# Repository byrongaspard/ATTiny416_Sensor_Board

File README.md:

# ATTiny416 Dev Board

This project is my first attempt at embedded hardware/software design where I layout/route a custom PCB. In my professional career, I have done schematic capture, integrated Arduino and Raspberry Pi like development boards into custom solutions, and developed embedded software, but this will be my first time laying out a custom circuit card.

There were no real requirements for this design as the primary objective was to learn how to layout a PCB using KiCad. However, to make the design process a little more interesting, I decided I wanted the board to have the following features:

- USB to UART communication to/from the microcontroller
- 3.3V microcontroller (instead of 5V)
- Includes SPI flash for recording data
- Accepts/regulates power from multiple inputs:
  - 5 V from USB
  - 30V from an external power source

The following image is the of the final board. The sections that follow will describe the more interesting portions of the design.

## Relevant Repository Links

- [KiCad Schematics](KiCad/): Contains the KiCad schematics for the electrical design
  - [Schematic Plots](KiCad/Plots/): Contains the PDF schematics plots for the electrical design
- [SPICE files](SPICE): Contains the LTSpice models used in the design
- [Code](Code): Contains the test code developed for the design

## Hardware Design

The first step in this hardware design was selecting a microcontroller. The ATTiny416 was chosen because of its interesting form factor. It comes in a very small (3x3mm) VQFN package while still providing a lot of the common/core Atmel peripherals found on larger microcontrollers. The USART and SPI peripheral were used in this project. This microcontroller also supports multiple logic levels, including 3.3V. The ATTiny416 is also very easy to integrate into a design as it requires almost no supporting external hardware.

A [ATTiny416 XPLAINED NANO](https://www.microchip.com/en-us/development-tool/attiny416-xnano) development board was purchased to support initial software development while waiting for the PCB to be manufactured/delivered.

### Power

The power design needed to provide the following features:

- Accept 5V USB input power
- Accept up to 30V of external input power
- Accept any combination of power inputs being present at the same time
- Preclude the backfeeding of power from input to input
- Provide a minimum of 50mA @ 3.3V whenever at least one input power is present
  - Provide uninterrupted power when power sources are applied and removed, so long as one input power source is present

The TPS7B6933 LDO linear regulator was selected to generate the 3.3V rail as the microcontroller, SPI flash, and USB to USART peripherals are all relatively low power devices and LDOs are among the simplest power supply designs to implement.
The TPS7B6933 can accept up to 40V (45V transient) of input voltage. The LDO is rated to provide 150mA of output current with a 14V input power source, therefore the maximum output current at 30V can be approximated to ~75mA, meeting the 50 mA requirement.

The simplest way to OR multiple power sources while precluding backfeeding of power would be a diode array. This was considered, but determined to not be feasible. The dropout voltage on the TPS7B6933 is 800mV, meaning 4.1V is the minimum input voltage required to maintain the 3.3V output (3.3V + 0.8V = 4.1V). Most diodes will have a forward voltage drop of approximately 0.7V. According to the USB spec, the minimum USB voltage available at peripherals is 4.35V. Therefore, after this 4.35V input USB power went through a diode, the voltage at the input to the LDO would be 3.65V (4.35V - 0.7V = 3.65V), which is below the TPS7B6933's minimum input voltage of 4.1V.

Therefore, an ideal diode circuit was designed to provide a smaller voltage drop when switching in the 5V USB input, while a regular diode was used to switch in the 30V input.
The DZDH0401DW P-Channel ideal diode controller was chosen primarily because of cost. An N-Channel ideal diode controller would have provided an even smaller voltage drop, but the design did not require this.
The DMP6110SVT was selected as the P-Channel FET primarily for it's relatively low R_DS(on) for a P-Channel FET of 130 mOhm. This R_DS(on) corresponds to a maximum voltage drop of 0.0065V across the FET at the maximum required 50mA output current (0.050A / 130mOhm = 0.0065V). This results in a minimum LDO input voltage of ~4.34VDC when only 5V USB power is present, well above the 4.1V minimum required by the TPS7B6933.

The BAT160 was selected as the diode to switch the 30V input. A LTSpice model was created to tune the ideal diode controller's resistors and to verify circuit functionality before manufacturing. The two images that follow are of the SPICE model where both 5V (4.35V) USB and 30V input power are switched while the 3.3V output is measured.

The colors in the time-base results that follow correspond to the following measurement points:

- Green: 30V input power
- Red: 5V (4.35V) USB input power
- Blue: ORed power from the BAT160 and DZDH0401DW ideal diode circuit
- Pink: 3.3V output power

Jumper resistors were also included in the design to allow the diode circuits to be reconfigured or bypassed entirely.

### USB to UART

The FT230 was selected to provide the USB to UART interface. This FTDI chip was chosen primarily for it's price. The FT230 datasheet recommended input USB data line filtering capacitors and termination resistors which were added to the design. LEDs were also added to CBUS1/2 on the FT230 to serve as Tx/Rx indicators.

The FT230 uses 5V logic levels on the USB inputs to comply with USB standards, but the UART output logic levels are configurable from 1.8-3.3V via the VCCIO input. The FT230 includes an internal 3.3V LDO on the 3V3OUT pin that can be connected directly to the VCCIO pin to provide the required 3.3V output logic levels. However, it is possible that the FT230's 3.3V regulator is outputting a higher voltage that the circuit card's main TPS7B6933 LDO. Therefore, the output of the design's main 3.3V LDO (TPS7B6933) was connected to the FT230's VCCIO input, instead of connecting the FT230's 3V3OUT.

Jumper resistors were included between the ATTiny416 and FT230 to support isolating the components if needed for debugging. Jumper resistors were also added to allow the FT230's 3V3OUT to be connected to VCCIO instead of the TPS7B6933's 3.3V output if needed.

The 5V USB power that is accepted on the mini-B USB input is also fused here before being utilized/regulated by the TPS7B6933.

### SPI Flash

The W25X20L SPI Flash chip was selected because it supported 3.3V logic levels. Otherwise, any generic SPI Flash chip would have been acceptable. The inverted logic write-protect, hold, and chip select signals were pulled up using external resistors. A debug header was added to all the SPI signal lines to support debugging with logic analyzers if needed. A 4.7uF decoupling capacitor was added to the W25X20L's input power line to provide more stable power, even though the datasheet did not explicitly it.

### PCB Design, Layout, and Manufacture

A two layer board was designed, The top layer contained signals/power and the bottom later was a ground plane. All components were manually placed and all traces were manually routed. The USB data lines were routed as differential pairs. The 32kHz oscillator was surrounded by a guard trace as recommended by the ATTiny416 datasheet. Copper pours were used in the power supply design as was recommended by the manufacturer.

The several copies of the PCB were ordered along with a solder paste stencil, as I would be manually assembling this board to support bring-up testing.

## Bring-up Testing

The circuit card was assembled and brought up in the following stages:

1. Power
2. UART
3. Microcontroller
4. SPI Flash

The hardware design was functional and did not require rework.

### Programming

There are multiple 3rd part, DIY, and OEM programmers for the ATTiny416 and other Atmel microcontrollers that use the UPDI interface. The [ICD 5](http://microchip.com/en-us/development-tool/dv164055) from Microchip is the latest OEM programmer and debugger, but it is quite expensive at ~$400. Instead, the [ATTiny416 XPLAINED NANO](https://www.microchip.com/en-us/development-tool/attiny416-xnano) development board was modified to act as a programmer. The dev board was modified by removing R200, which connects the dev board's ATmega32U4 programmer to the dev board's ATTiny416.

Finally, the GND and the ATmega32U4 programmer UPDI output pin could be connected to the programming header on the custom circuit card as shown in the figure below:

When the ATTiny416 is running on 3.3V input power, none of it's GPIO pins are 5V tolerant, except the reset/programming pin. The reset/programming pin (PA0) can accept up to 12.5V to support the chip's high-voltage reset functionality when PA0 is configured by software as GPIO. This 12.5V tolerance allows 5V logic levels to be used when programming this 3.3V microcontroller without damage.

## Software Design

The objective of the software design was to verify the functionality of all hardware design. To accomplish this, test software was written that provides the following functionality:

- Write a known pattern of data to SPI Flash
- Provide an external command to export the contents of SPI Flash
- Provide an external command to erase the SPI Flash

The code was developed in the MPLAB X IDE and can be found [here](Code), but the diagram that follows describes the high-level code execution flow.

```mermaid
flowchart LR
    Z["Wait forever until reset (Infinite Loop)."]
    A[Start] --> B[Initialize uC GPIO and peripherals]
    B --> C{Dump Flash Command Asserted?}
    C --> |YES| D[Dump Flash over UART.]
    D --> Z
    C --> |NO| E{Erase Flash Command Asserted?}
    E --> |YES| F[Erase Flash and notify when erase is complete over UART.]
    F --> Z
    E --> |NO| G{Is storage remaining in Flash?}
    G --> |YES| H[Write data pattern to Flash.]
    H --> G
    G --> |NO| Z
```

The external commands to export and erase SPI Flash were implemented using two ATTiny416 GPIO interfaces:

- PA6 = ERASE_N
- PA7 = DUMP_N

The ATTiny416's internal pull-up resistors were enabled for the dump and erase pin (PA6 & PA7). The software then uses inverted logic at initialization when interpreting these pins to decide when to erase and dump Flash.

To erase Flash, an operator would:

1. Connect PA6 to GND
2. Reset the ATTiny416
3. UART interface can be monitored for software indication of erase completion.

Similarly, to dump Flash, an operator would:

1. Connect PA7 to GND
2. Reset the ATTiny416
3. Receive the contents of Flash over the UART interface.

The dump Flash command is given priority over the erase Flash command, so if both are ever asserted at the same time, the ATTiny416 will dump the contents of Flash instead of erasing.

These command interfaces are only interrogated by software during initialization. If neither are asserted when the microcontroller is released from reset, the normal Flash recording loop will be entered. Inverted logic is used for these interfaces to protect the ATTiny416 from expected behavior caused by applying voltage to GPIO pins while no power is applied to the microcontroller itself.

The FT230 to ATTiny416 serial receive functionality was verified in bring-up test code that was not included in this repository.

### Software Testing Results

The screen captures that follow are of the ATTiny416's UART outputs while testing software.

The following screenshot shows three separate boot events, each starting with the "Booting..." text. When the software initializes, it determines that neither of the erase or dump flash inputs are asserted, and proceeds to enter the recording loop. To find where the software can begin writing to without overwriting previously recorded data, the software iterates through all of flash until it finds uninitialized memory (0xFF).

The first boot shown occurred right after SPI flash was erased, as the start of memory was detected at the 0x0000 address. The second boot shown occurred after some of flash has been written to, as the start of memory is reported as 0x001010, instead of 0x000000. The program was then allowed to run until flash was completely full, which was when the "Aborting W25X20L write... not enough memory left" message was printed. The third and final boot shown occurred after SPI flash was completely full, which is why the software was unable to find uninitialized flash and the "Could not find start of memory" message was printed.

The next two images show the UART output when the dump flash command was asserted at reset. The entire contents of the W25X20L flash area printed to the console in HEX, followed by a two's-compliment checksum.

The final image below shows the UART output when the erase flash command was asserted at reset. The software reports when the W25X20L chip has completed erasing.

# Summary

This project was a lot of fun and gave me a lot more confidence with the PCB layout portions of hardware design. The layout requirements for this design were very simple as we didn't have to contend with high-power, high-speed signals, noise, etc., but it was still a fun and rewarding learning experience for me.

## Additional Work

The following can still be completed on this project:

- Test the external 32kHz crystal oscillator

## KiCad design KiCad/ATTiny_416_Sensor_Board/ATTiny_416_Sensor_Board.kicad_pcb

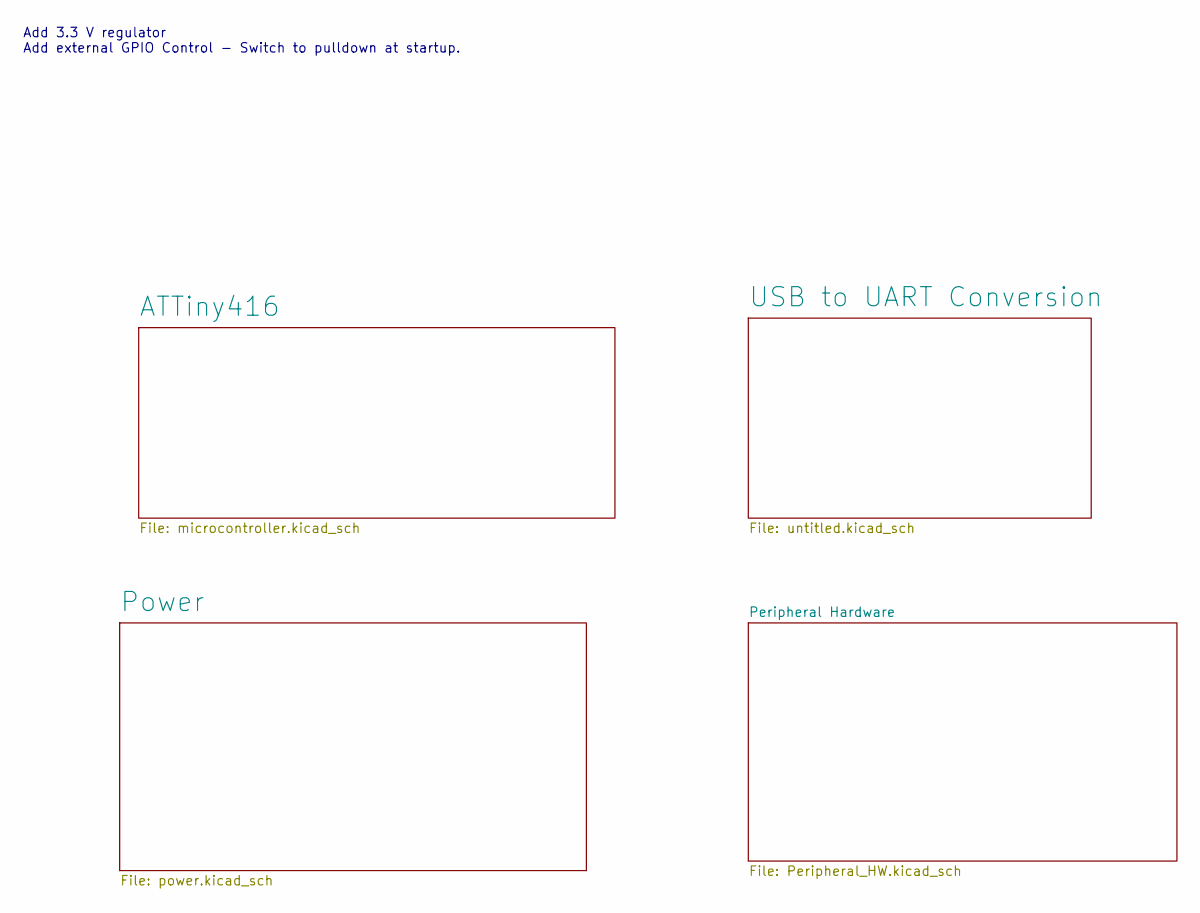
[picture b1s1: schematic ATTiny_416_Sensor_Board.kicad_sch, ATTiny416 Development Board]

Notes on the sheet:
Add 3.3 V regulator Add external GPIO Control - Switch to pulldown at startup.

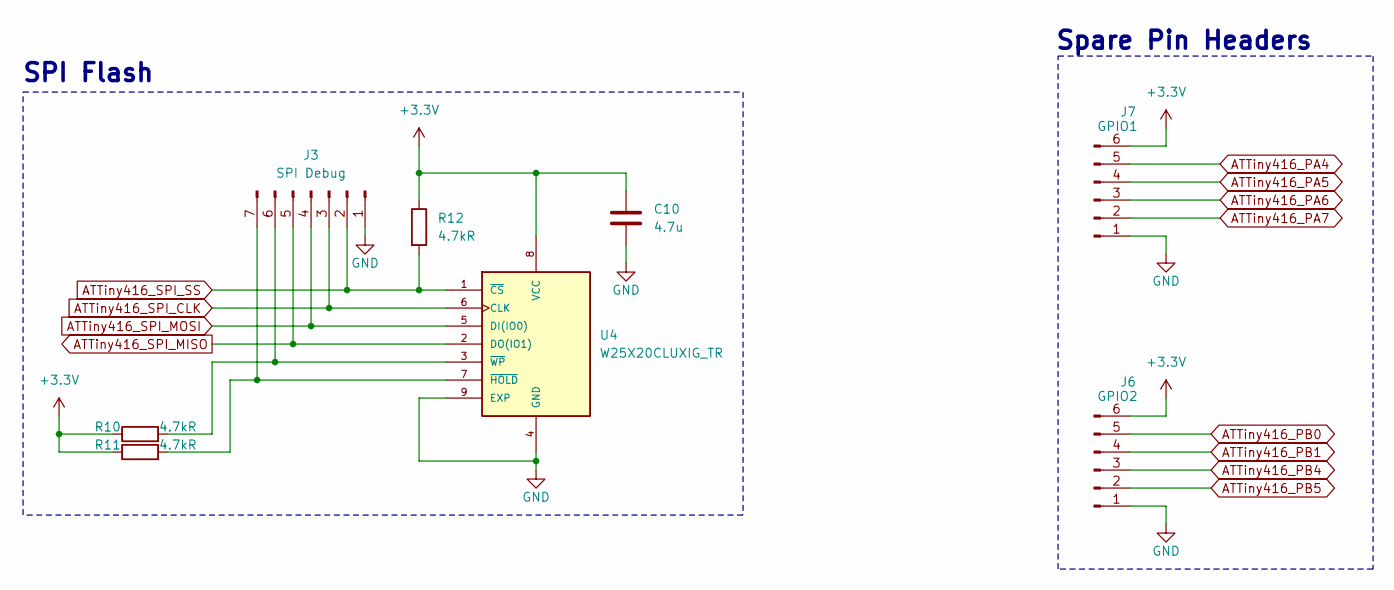
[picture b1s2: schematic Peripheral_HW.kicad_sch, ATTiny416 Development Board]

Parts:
C10: 4.7u; C_0805_2012Metric_Pad1.18x1.45mm_HandSolder
J3: SPI Debug; PinHeader_1x07_P2.54mm_Vertical
J6: GPIO2; PinHeader_1x06_P2.54mm_Vertical
J7: GPIO1; PinHeader_1x06_P2.54mm_Vertical
R10, R11, R12: 4.7kR; R_0805_2012Metric_Pad1.20x1.40mm_HandSolder
U4: W25X20CLUXIG_TR; W25X20CLUXIG TR

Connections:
+3.3V: C10.1, J6.6, J7.6, R10.1, R11.1, R12.1, U4.8 (VCC); also elsewhere on the board
ATTiny416_PA4: J7.5; also elsewhere on the board
ATTiny416_PA5: J7.4; also elsewhere on the board
ATTiny416_PA6: J7.3; also elsewhere on the board
ATTiny416_PA7: J7.2; also elsewhere on the board
ATTiny416_PB0: J6.5; also elsewhere on the board
ATTiny416_PB1: J6.4; also elsewhere on the board
ATTiny416_PB4: J6.3; also elsewhere on the board
ATTiny416_PB5: J6.2; also elsewhere on the board
ATTiny416_SPI_CLK: J3.3, U4.6 (CLK); also elsewhere on the board
ATTiny416_SPI_MISO: J3.5, U4.2 (DO(IO1)); also elsewhere on the board
ATTiny416_SPI_MOSI: J3.4, U4.5 (DI(IO0)); also elsewhere on the board
ATTiny416_SPI_SS: J3.2, R12.2, U4.1 (~CS); also elsewhere on the board
GND: C10.2, J3.1, J6.1, J7.1, U4.4 (GND), U4.9 (EXP); also elsewhere on the board
unnamed: J3.6, R10.2, U4.3 (~WP)
unnamed: J3.7, R11.2, U4.7 (~HOLD)

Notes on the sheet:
Spare Pin Headers
SPI Flash

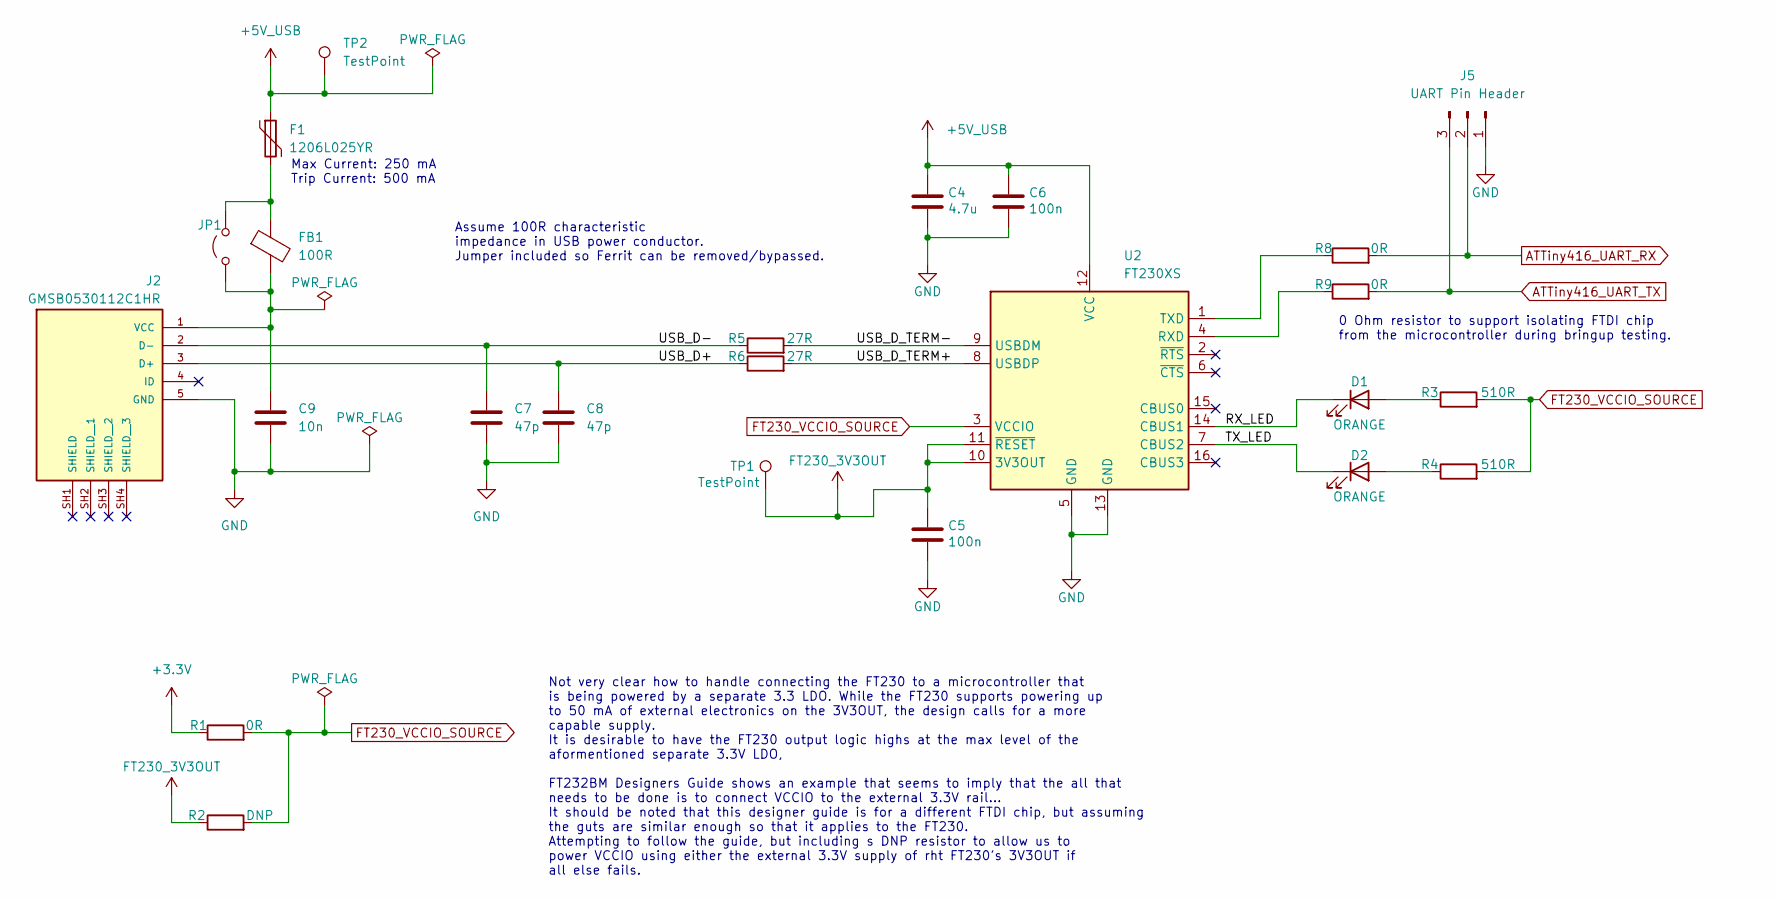
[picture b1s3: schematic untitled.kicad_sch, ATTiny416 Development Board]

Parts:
C4: 4.7u; C_0805_2012Metric_Pad1.18x1.45mm_HandSolder
C5, C6: 100n; C_0805_2012Metric_Pad1.18x1.45mm_HandSolder
C7, C8: 47p; C_0805_2012Metric_Pad1.18x1.45mm_HandSolder
C9: 10n; C_0805_2012Metric_Pad1.18x1.45mm_HandSolder
D1, D2: ORANGE; D_0805_2012Metric_Pad1.15x1.40mm_HandSolder
F1: 1206L025YR; Fuse_1206_3216Metric
FB1: 100R; R_1206_3216Metric_Pad1.30x1.75mm_HandSolder
J2: GMSB0530112C1HR; AMPHENOL_GMSB0530112C1HR; PARTREV AX4
J5: UART Pin Header; PinHeader_1x03_P2.54mm_Vertical
JP1: SolderJumper-2_P1.3mm_Open_RoundedPad1.0x1.5mm
R1, R8, R9: 0R; R_0805_2012Metric_Pad1.20x1.40mm_HandSolder
R2: DNP; R_0805_2012Metric_Pad1.20x1.40mm_HandSolder
R3, R4: 510R; R_0805_2012Metric_Pad1.20x1.40mm_HandSolder
R5, R6: 27R; R_0805_2012Metric_Pad1.20x1.40mm_HandSolder
TP1, TP2: TestPoint; TestPoint_Pad_D2.5mm
U2: FT230XS; SSOP-16_3.9x4.9mm_P0.635mm

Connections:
+3.3V: R1.1; also elsewhere on the board
+5V_USB: C4.1, C6.1, F1.1, TP2.1, U2.12 (VCC); also elsewhere on the board
/USB to UART Conversion/RX_LED: D1.1 (K), U2.14 (CBUS1)
/USB to UART Conversion/TX_LED: D2.1 (K), U2.7 (CBUS2)
/USB to UART Conversion/USB_D+: C8.1, J2.3 (D+), R6.1
/USB to UART Conversion/USB_D-: C7.1, J2.2 (D-), R5.1
/USB to UART Conversion/USB_D_TERM+: R6.2, U2.8 (USBDP)
/USB to UART Conversion/USB_D_TERM-: R5.2, U2.9 (USBDM)
ATTiny416_UART_RX: J5.2, R8.2; also elsewhere on the board
ATTiny416_UART_TX: J5.3, R9.2; also elsewhere on the board
FT230_3V3OUT: C5.1, R2.1, TP1.1, U2.10 (3V3OUT), U2.11 (~RESET)
FT230_VCCIO_SOURCE: R1.2, R2.2, R3.2, R4.2, U2.3 (VCCIO)
GND: C4.2, C5.2, C6.2, C7.2, C8.2, C9.2, J2.5 (GND), J5.1, U2.5 (GND), U2.13 (GND); also elsewhere on the board
unnamed: D1.2 (A), R3.1
unnamed: D2.2 (A), R4.1
unnamed: C9.1, FB1.2, J2.1 (VCC), JP1.1 (A)
unnamed: F1.2, FB1.1, JP1.2 (B)
unnamed: R9.1, U2.4 (RXD)
unnamed: R8.1, U2.1 (TXD)

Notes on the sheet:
Not very clear how to handle connecting the FT230 to a microcontroller that is being powered by a separate 3.3 LDO. While the FT230 supports powering up to 50 mA of external electronics on the 3V3OUT, the design calls for a more capable supply. It is desirable to have the FT230 output logic highs a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
0 Ohm resistor to support isolating FTDI chip from the microcontroller during bringup testing.
Assume 100R characteristic impedance in USB power conductor. Jumper included so Ferrit can be removed/bypassed.
Max Current: 250 mA Trip Current: 500 mA

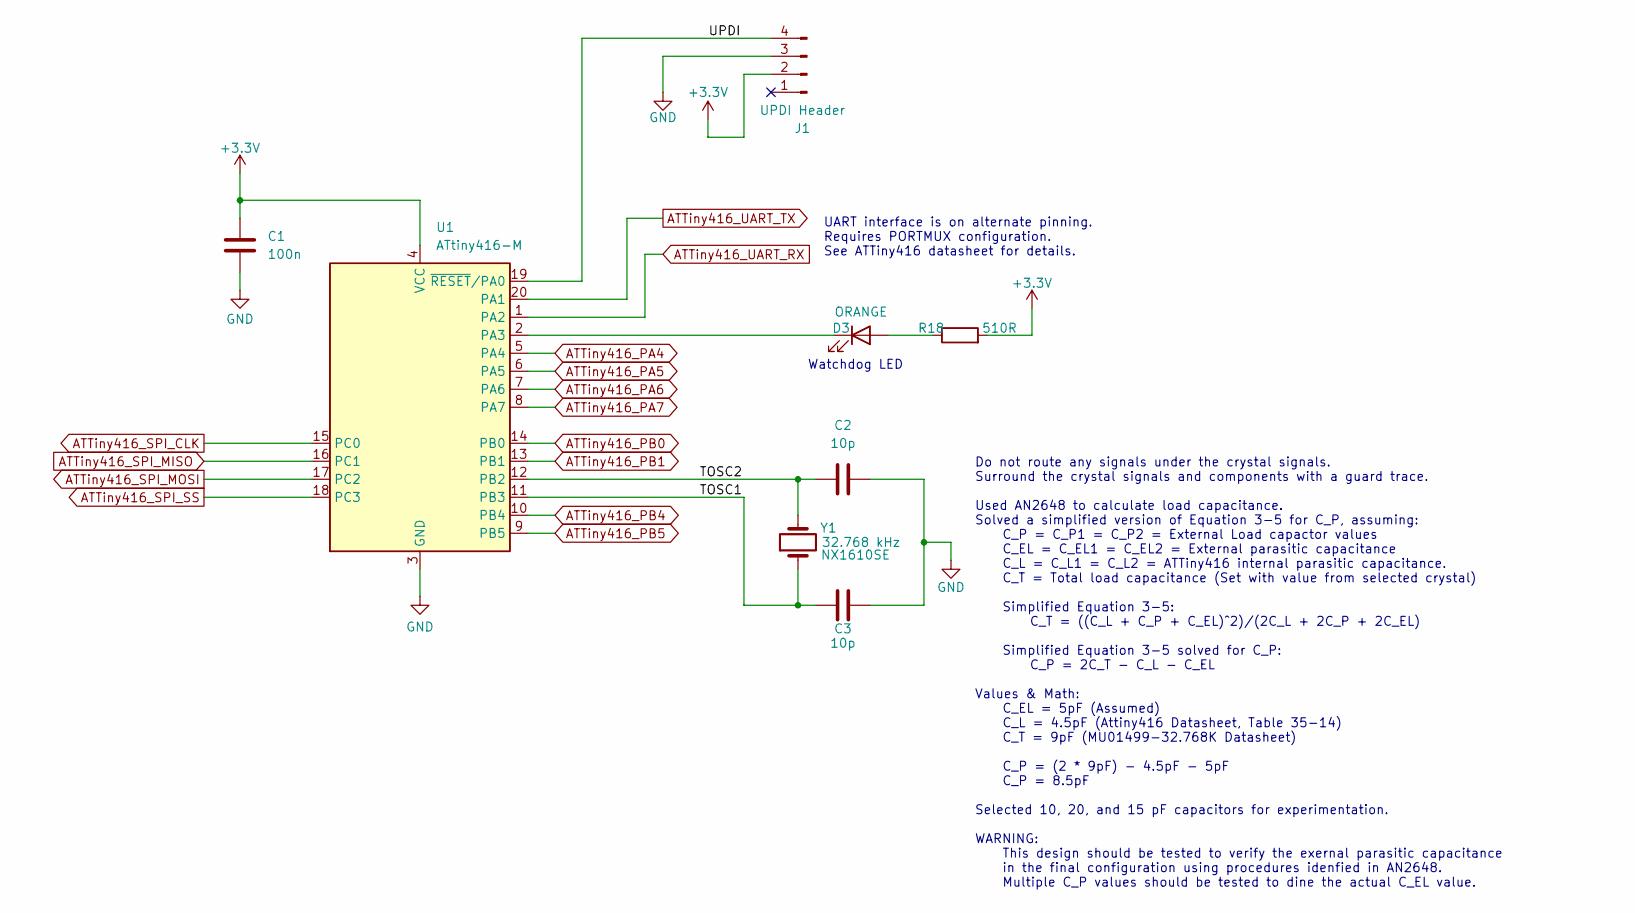
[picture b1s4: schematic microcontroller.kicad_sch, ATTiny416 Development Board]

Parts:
C1: 100n; C_0805_2012Metric_Pad1.18x1.45mm_HandSolder
C2, C3: 10p; C_0805_2012Metric_Pad1.18x1.45mm_HandSolder
D3: ORANGE; D_0805_2012Metric_Pad1.15x1.40mm_HandSolder
J1: UPDI Header; PinHeader_1x04_P2.54mm_Vertical
R18: 510R; R_0805_2012Metric_Pad1.20x1.40mm_HandSolder
U1: ATtiny416-M; VQFN-20-1EP_3x3mm_P0.4mm_EP1.7x1.7mm
Y1: 32.768 kHz; NX1610SE

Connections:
+3.3V: C1.1, J1.2, R18.2, U1.4 (VCC); also elsewhere on the board
/ATTiny416/TOSC1: C3.1, U1.11 (PB3), Y1.1
/ATTiny416/TOSC2: C2.1, U1.12 (PB2), Y1.2
/ATTiny416/UPDI: J1.4, U1.19 (~RESET/PA0)
ATTiny416_PA4: U1.5 (PA4); also elsewhere on the board
ATTiny416_PA5: U1.6 (PA5); also elsewhere on the board
ATTiny416_PA6: U1.7 (PA6); also elsewhere on the board
ATTiny416_PA7: U1.8 (PA7); also elsewhere on the board
ATTiny416_PB0: U1.14 (PB0); also elsewhere on the board
ATTiny416_PB1: U1.13 (PB1); also elsewhere on the board
ATTiny416_PB4: U1.10 (PB4); also elsewhere on the board
ATTiny416_PB5: U1.9 (PB5); also elsewhere on the board
ATTiny416_SPI_CLK: U1.15 (PC0); also elsewhere on the board
ATTiny416_SPI_MISO: U1.16 (PC1); also elsewhere on the board
ATTiny416_SPI_MOSI: U1.17 (PC2); also elsewhere on the board
ATTiny416_SPI_SS: U1.18 (PC3); also elsewhere on the board
ATTiny416_UART_RX: U1.1 (PA2); also elsewhere on the board
ATTiny416_UART_TX: U1.20 (PA1); also elsewhere on the board
GND: C1.2, C2.2, C3.2, J1.3, U1.3 (GND), U1.21 (GND); also elsewhere on the board
unnamed: D3.2 (A), R18.1
unnamed: D3.1 (K), U1.2 (PA3)

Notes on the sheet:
Do not route any signals under the crystal signals. Surround the crystal signals and components with a guard trace. Used AN2648 to calculate load capacitance. Solved a simplified version of Equation 3-5 for C_P, assuming: C_P = C_P1 = C_P2 = External Load capactor values C_EL = C_EL1 = C_EL2 = Exte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
UART interface is on alternate pinning. Requires PORTMUX configuration. See ATTiny416 datasheet for details.
Watchdog LED

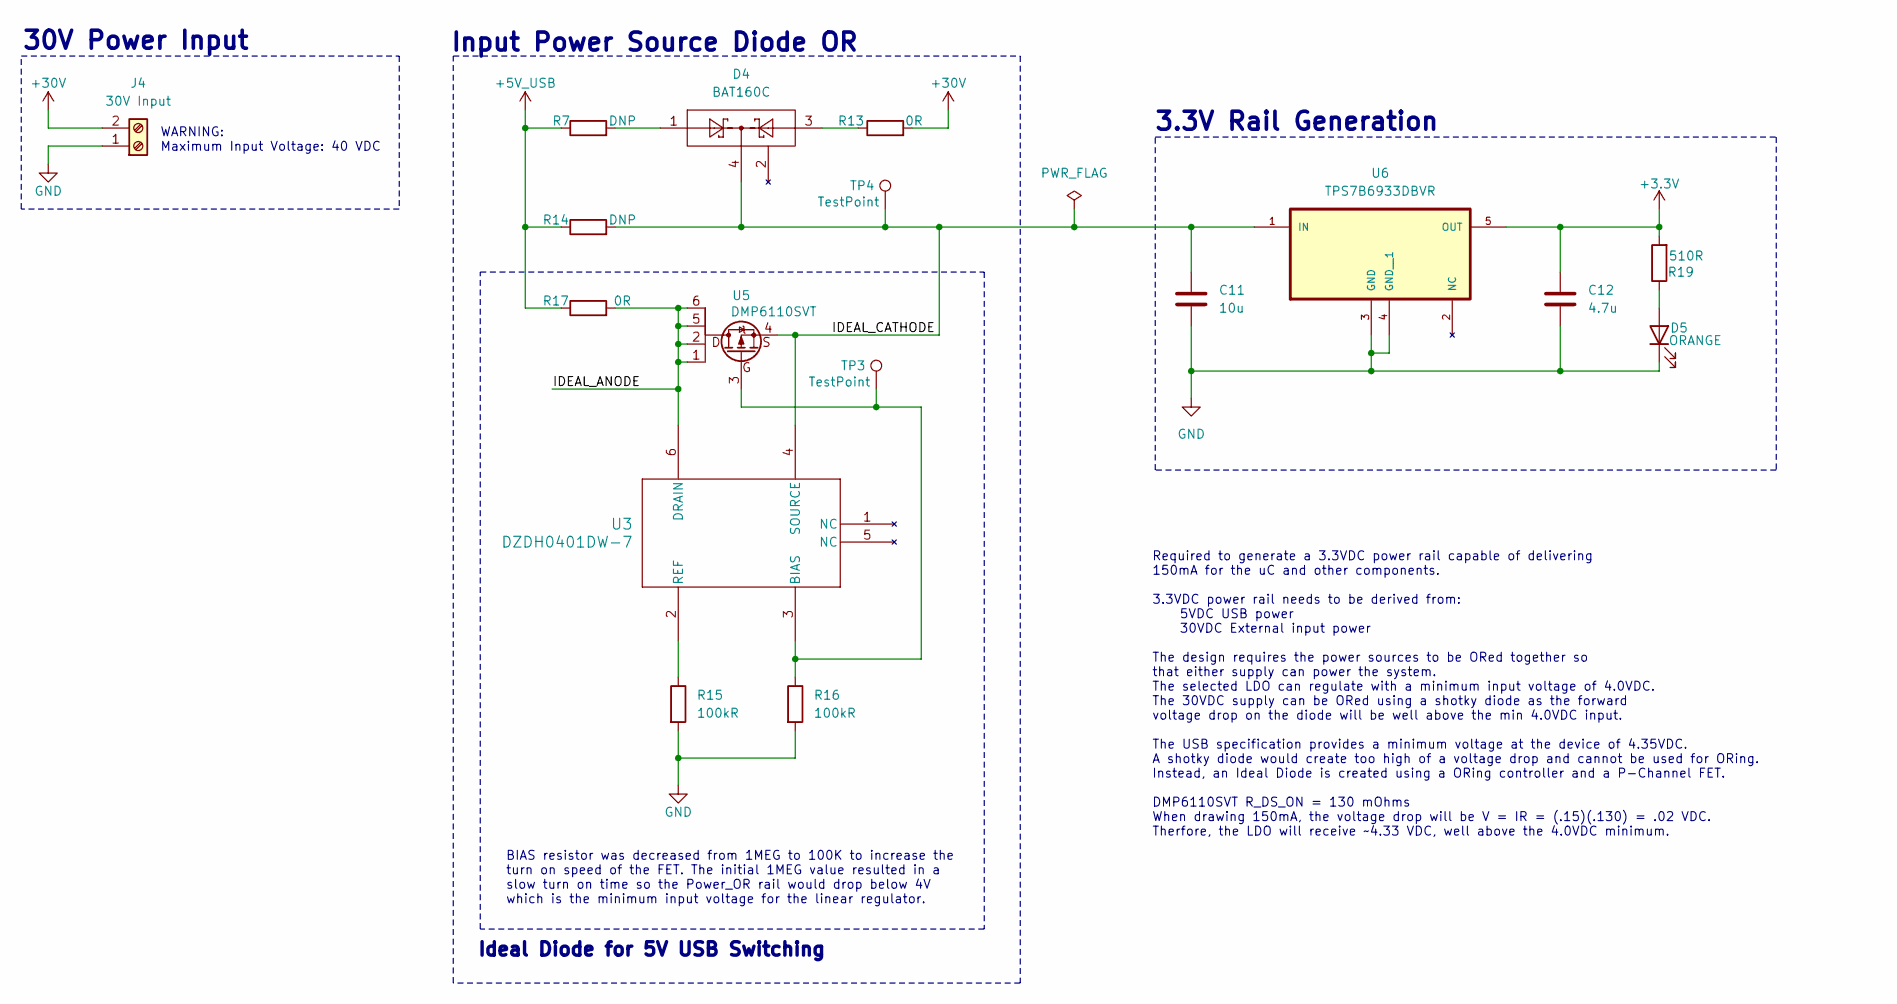
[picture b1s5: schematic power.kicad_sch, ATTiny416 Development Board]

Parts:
C11: 10u; C_1210_3225Metric_Pad1.33x2.70mm_HandSolder
C12: 4.7u; C_0805_2012Metric_Pad1.18x1.45mm_HandSolder
D4: BAT160C; SOT-223
D5: ORANGE; D_0805_2012Metric_Pad1.15x1.40mm_HandSolder
J4: 30V Input; Two_Position_Screw_Terminal
R7, R14: DNP; R_0805_2012Metric_Pad1.20x1.40mm_HandSolder
R13, R17: 0R; R_0805_2012Metric_Pad1.20x1.40mm_HandSolder
R15, R16: 100kR; R_0805_2012Metric_Pad1.20x1.40mm_HandSolder
R19: 510R; R_0805_2012Metric_Pad1.20x1.40mm_HandSolder
TP3, TP4: TestPoint; TestPoint_Pad_D2.5mm
U3: DZDH0401DW-7; SOT-363_SC-70-6_Handsoldering
U5: DMP6110SVT
U6: TPS7B6933DBVR; SOT-23-5

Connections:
+3.3V: C12.2, R19.2, U6.5 (OUT); also elsewhere on the board
+5V_USB: R7.1, R14.1, R17.1; also elsewhere on the board
+30V: J4.2, R13.2
/Power/IDEAL_ANODE: R17.2, U3.6 (DRAIN), U5.1, U5.2, U5.5, U5.6
/Power/IDEAL_CATHODE: C11.2, D4.4, R14.2, TP4.1, U3.4 (SOURCE), U5.4, U6.1 (IN)
GND: C11.1, C12.1, D5.1 (K), J4.1, R15.2, R16.2, U6.3 (GND), U6.4 (GND__1); also elsewhere on the board
unnamed: D4.1, R7.2
unnamed: D4.3, R13.1
unnamed: D5.2 (A), R19.1
unnamed: R16.1, TP3.1, U3.3 (BIAS), U5.3
unnamed: R15.1, U3.2 (REF)

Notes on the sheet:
Input Power Source Diode OR
WARNING: Maximum Input Voltage: 40 VDC
30V Power Input
Ideal Diode for 5V USB Switching
Required to generate a 3.3VDC power rail capable of delivering 150mA for the uC and other components. 3.3VDC power rail needs to be derived from: 5VDC USB power 30VDC External input power The design requires the power sources to be ORed together so that either supply can power the system. The selec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
BIAS resistor was decreased from 1MEG to 100K to increase the turn on speed of the FET. The initial 1MEG value resulted in a slow turn on time so the Power_OR rail would drop below 4V which is the minimum input voltage for the linear regulator.
3.3V Rail Generation

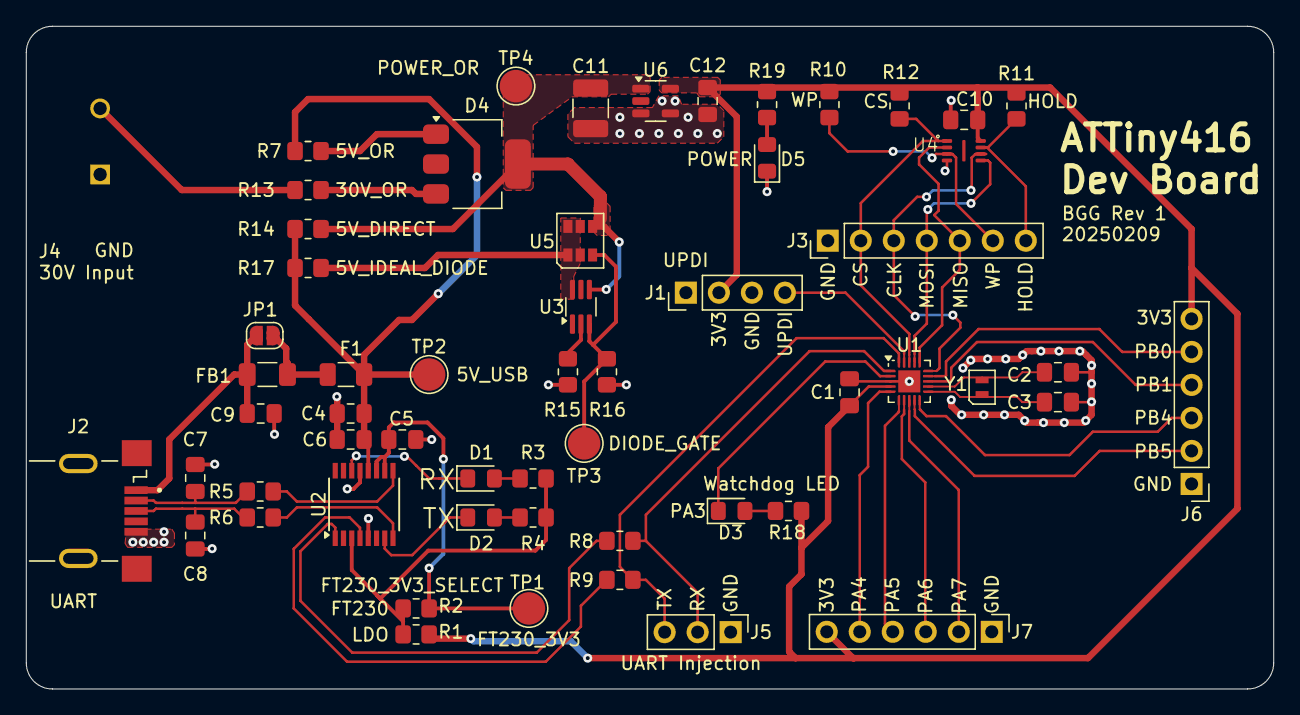
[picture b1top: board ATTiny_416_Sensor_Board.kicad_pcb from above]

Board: 2 copper layers, 96.0 x 51.0 mm, 57 parts (0 on the bottom side), 46 nets.

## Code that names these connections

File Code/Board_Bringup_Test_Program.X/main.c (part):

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 * It initializes an external serial communication interface to the FTDI230 chip.
 * Additionally, it exercises the external W25X20L flash chip.
 * 
 * Connecting PA6 to ground will cause the ATTiny416 to dump the contents of
 * the W25X20L flash to the UART interface. 
 * Connecting PA7 to ground will cause the ATTiny416 to erase the W25X20L flash.
 * If both PA6 and PA7 are left floating, the ATTiny416 will look for the beginning
 * of uninitialized flash and begin recording data.
 * 
 * TODO: Separate code out into logical *.c and *.h files. 
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   
    if(!GET_BIT(PORTA.IN, 6))
    {
        send_uart_string("PA6 is LOW. Dumping Flash\n");
        W25X20L_dump_flash_to_uart();
        send_uart_string("\n\nFlash dump complete! Reboot required.\n");
        while(1);
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    
    if(!GET_BIT(PORTA.IN, 7))
    {
        send_uart_string("PA7 is LOW. Erasing Flash. \n");
        W25X20L_chip_erase();
        send_uart_string("Reboot required. \n");
        while(1);
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        if(GET_BIT(PORTA.IN, 6))
        {
            W25X20L_write_enable();
            //send_uart_string("PA6 is HIGH. Recording Data. \n");
            W25X20L_write_data(test_arr, sizeof(test_arr)/sizeof(test_arr[0]));
            test_arr[0]++;
        }
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void configure_data_direction(void)
{
    // USART Configuration
        SET_BIT(PORTA.OUT, 1);  // TxD is on PA1. Initialize HIGH (idle).
        SET_BIT(PORTA.DIR, 1);  // TxD is on PA1. Initialize as output.
        CLR_BIT(PORTA.DIR, 2);  // RxD is on PA2. Initialize as input.

    // SPI Configuration
        CLR_BIT(PORTC.OUT, 0);  // CLK is on PC0. Initialize low.
        SET_BIT(PORTC.DIR, 0);  // CLK is on PC0. Initialize as output.

        CLR_BIT(PORTC.DIR, 1);  // MISO is on PC1. Initialize as input.

        CLR_BIT(PORTC.OUT, 2);  // MOSI is on PC2. Initialize low. 
        SET_BIT(PORTC.DIR, 2);  // MOSI is on PC2. Initialize as output. 

        SET_BIT(PORTC.OUT, 3);  // CS/SS is on PC3. Initialize high.
        SET_BIT(PORTC.DIR, 3);  // CS/SS is on PC3. Configure as output. 
    
    // LED Configuration
        CLR_BIT(PORTA.OUT, 3); // LED is on PA3. Initialize ON.
        SET_BIT(PORTA.DIR, 3); // LED is on PA3. Configure as output.
        
    // GPIO Configuration
        CLR_BIT(PORTA.DIR, 7);      // GPIO input on PA7
        SET_BIT(PORTA.PIN7CTRL, 3); // Enable pull-up resistor
       
        CLR_BIT(PORTA.DIR, 6);      // GPIO input on PA6
        SET_BIT(PORTA.PIN6CTRL, 3); // Enable pull-up resistor

    return;
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{
    if(val == ASSERT_SELECT)
    {
        CLR_BIT(PORTC.OUT, 3);  // CS/SS is on PC3. Set LOW to select chip.
    }
    else
    {
        SET_BIT(PORTC.OUT, 3);  // CS/SS is on PC3. Set LOW to select chip.
    }
}

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
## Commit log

2025-02-15 Initial release for mfr
2025-02-15 created gitignore and removed junk files
2025-02-16 including first schematic revision plot
2025-02-16 Initial code for board bringup
2025-02-16 cleaning up kicad docs
2025-02-16 Cleaned up Schematics
2025-02-17 Bringup code updated to exercise SPI and UART interaces
2025-02-17 code cleanup
2025-02-17 Fixed code that was incorrectly checking for the end of flash and allowing end of flash to go unused. Added two's compliment checksum when dumping flash
2025-04-05 Fixed no-erase bug by ensuring SPI chip has writes enabled before sending erase command
2025-04-05 updated gitignore for MPLAB projects to exclude an additional log file
2025-04-05 removed bad schematic notes and re-plotted
2025-04-05 added project pictures for readme
2025-04-05 Update README.md
    Added pictures to readme
2025-04-05 Update README.md
    Started writing description
2025-04-05 Added more images and datasheets
2025-04-05 updated USB input voltage to the correct minimum (4.35).
2025-04-05 corrected picture
2025-04-06 added diagrams and fixed spelling errors
2025-04-06 Updated documentation
2025-04-06 Updated readme and added more pictures/datasheets
2025-05-05 cleaned up readme
